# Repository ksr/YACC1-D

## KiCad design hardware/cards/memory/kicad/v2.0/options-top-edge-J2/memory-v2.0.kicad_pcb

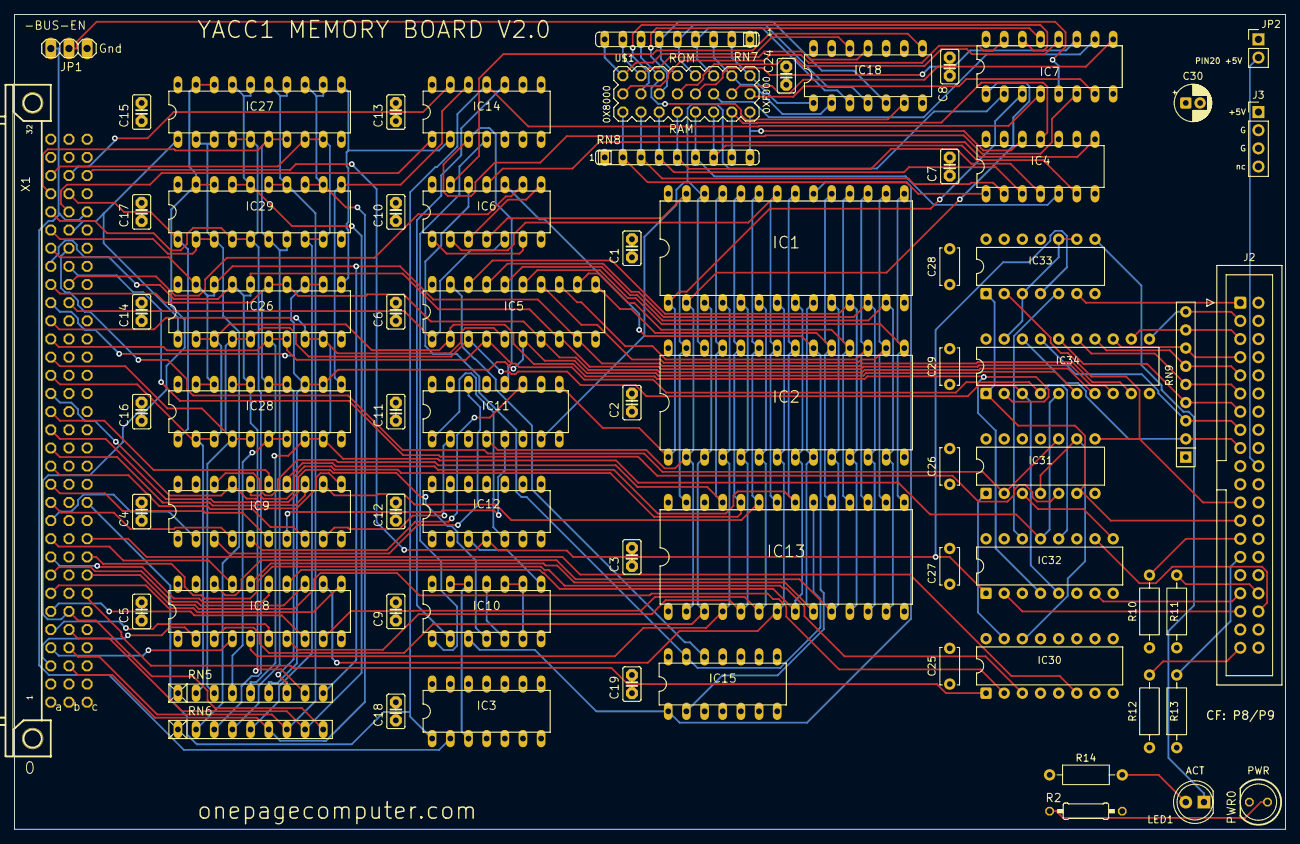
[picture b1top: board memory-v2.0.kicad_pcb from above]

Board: 4 copper layers, 177.8 x 114.0 mm, 70 parts (0 on the bottom side), 148 nets.

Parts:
C1, C2, C3, C4, C5, C6, C7, C8, C9, C10, C11, C12, C13, C14, C15, C16, C17, C18, C19, C24: C025-025X050
C25, C26, C27, C28, C29: 100n; C_Disc_D5.0mm_W2.5mm_P5.00mm
C30: 10u; CP_Radial_D5.0mm_P2.00mm
IC1, IC2, IC13: DIL28-6
IC3: 74LS32N; DIL14
IC4, IC18: 74ALS30N; DIL14
IC5: 74LS245N; DIL20
IC6, IC14: 74LS04N; DIL14
IC7: 74LS138N; DIL16
IC8, IC9: 74LS244N; DIL20
IC10: 74ALS00N; DIL14
IC11: 74LS157N; DIL16
IC12: 74LS74N; DIL14
IC15: 74ALS11N; DIL14
IC26, IC27, IC28, IC29: 74LS374N; DIL20
IC30: 74LS138; DIP-16_W7.62mm
IC31: 74LS32; DIP-14_W7.62mm
IC32: 74LS175; DIP-16_W7.62mm
IC33: 74LS08; DIP-14_W7.62mm
IC34: 74LS245; DIP-20_W7.62mm
J2: IDE 40; IDC-Header_2x20_P2.54mm_Vertical
J3: POWER; PinHeader_1x04_P2.54mm_Vertical
JP1: 1X03
JP2: PIN20 5V; PinHeader_1x02_P2.54mm_Vertical
LED1: ACT yellow; LED_D5.0mm
PWR0: LED5MM
R2: 330; 0207_10
R10, R11, R12, R13: 10k; R_Axial_DIN0207_L6.3mm_D2.5mm_P10.16mm_Horizontal
R14: 1k; R_Axial_DIN0207_L6.3mm_D2.5mm_P10.16mm_Horizontal
RN5, RN6: RN-9
RN7, RN8: SIL9
RN9: 10k x8; R_Array_SIP9
U$1: PIN_3X8
X1: FABC96R

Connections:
-BUS-EN: IC3.2, JP1.1, X1.C28
-HI-RAM: IC2.20, IC6.10, IC15.2
-IO-RD: IC31.5, X1.B25
-IO-WR: IC31.2, IC31.10, X1.B26
-LO-RAM: IC1.20, IC10.3, IC15.1
-MEM-RD: IC5.1, IC6.5, X1.B23
-MEM-WR: IC6.9, X1.B24
-RESET: IC12.4, IC32.1, IC33.4, X1.C30
-ROM-CS: IC6.12, IC13.20, IC15.13
-TMP-REG-LD0: IC14.1, X1.B28
-TMP-REG-LD1: IC14.13, X1.B30
-TMP-REG-RD0: IC26.1, IC27.1, X1.B27
-TMP-REG-RD1: IC28.1, IC29.1, X1.B29
-VMA: IC3.1, IC7.4, IC14.11, X1.C12
/Sheet 2/RAM0: IC4.1, RN8.2, U$1.17
/Sheet 2/RAM1: IC4.2, RN8.3, U$1.18
/Sheet 2/RAM2: IC4.3, RN8.4, U$1.19
/Sheet 2/RAM3: IC4.4, RN8.5, U$1.20
/Sheet 2/RAM4: IC4.5, RN8.6, U$1.21
/Sheet 2/RAM5: IC4.6, RN8.7, U$1.22
/Sheet 2/RAM6: IC4.11, RN8.8, U$1.23
/Sheet 2/RAM7: IC4.12, RN8.9, U$1.24
/Sheet 2/ROM0: IC18.12, RN7.9, U$1.1
/Sheet 2/ROM1: IC18.11, RN7.8, U$1.2
/Sheet 2/ROM2: IC18.6, RN7.7, U$1.3
/Sheet 2/ROM3: IC18.5, RN7.6, U$1.4
/Sheet 2/ROM4: IC18.4, RN7.5, U$1.5
/Sheet 2/ROM5: IC18.3, RN7.4, U$1.6
/Sheet 2/ROM6: IC18.2, RN7.3, U$1.7
/Sheet 2/ROM7: IC18.1, RN7.2, U$1.8
/Sheet 2/SEL0: IC7.15, U$1.9
/Sheet 2/SEL1: IC7.14, U$1.10
/Sheet 2/SEL2: IC7.13, U$1.11
/Sheet 2/SEL3: IC7.12, U$1.12
/Sheet 2/SEL4: IC7.11, U$1.13
/Sheet 2/SEL5: IC7.10, U$1.14
/Sheet 2/SEL6: IC7.9, U$1.15
/Sheet 2/SEL7: IC7.7, U$1.16
/Sheet 7/-CFOE: IC33.3, IC33.9, IC33.10, IC34.19
/Sheet 7/-CFRESET: IC33.6, J2.1
/Sheet 7/-DASP: J2.39, R12.2
/Sheet 7/-DMACK: J2.29, R13.2
/Sheet 7/-IOR: IC31.6, IC33.1, IC34.1, J2.25
/Sheet 7/-IOW: IC31.8, IC33.2, J2.23
/Sheet 7/-P8SEL: IC30.15, IC31.1
/Sheet 7/-P9SEL: IC30.14, IC31.4, IC31.9
/Sheet 7/-PDIAG: J2.34, R11.2
/Sheet 7/-SRST: IC32.14, IC33.5
/Sheet 7/ACTK: IC33.8, LED1.1
/Sheet 7/CFD0: IC34.18, J2.17, RN9.2
/Sheet 7/CFD1: IC34.17, J2.15, RN9.3
/Sheet 7/CFD2: IC34.16, J2.13, RN9.4
/Sheet 7/CFD3: IC34.15, J2.11, RN9.5
/Sheet 7/CFD4: IC34.14, J2.9, RN9.6
/Sheet 7/CFD5: IC34.13, J2.7, RN9.7
/Sheet 7/CFD6: IC34.12, J2.5, RN9.8
/Sheet 7/CFD7: IC34.11, J2.3, RN9.9
/Sheet 7/DA0: IC32.2, J2.35
/Sheet 7/DA1: IC32.7, J2.33
/Sheet 7/DA2: IC32.10, J2.36
/Sheet 7/IORDY: J2.27, R10.2
/Sheet 7/LATCHCLK: IC31.3, IC32.9
/Sheet 7/LEDA2: LED1.2, R14.2
/Sheet 7/PIN20: J2.20, JP2.2
ADDR0: IC8.2, X1.A3
ADDR1: IC8.4, X1.A4
ADDR2: IC8.6, X1.A5
ADDR3: IC8.8, X1.A6
ADDR4: IC8.11, X1.A7
ADDR5: IC8.13, X1.A8
ADDR6: IC8.15, X1.A9
ADDR7: IC8.17, X1.A10
ADDR8: IC9.2, X1.A11
ADDR9: IC9.4, X1.A12
ADDR10: IC9.6, X1.A13
ADDR11: IC9.8, X1.A14
ADDR12: IC9.11, X1.A15
ADDR13: IC9.13, X1.A16
ADDR14: IC9.15, X1.A17
ADDR15: IC9.17, IC10.4, X1.A18
BADDR0: IC1.10, IC2.10, IC8.18, IC13.10
BADDR1: IC1.9, IC2.9, IC8.16, IC13.9
BADDR2: IC1.8, IC2.8, IC8.14, IC13.8
BADDR3: IC1.7, IC2.7, IC8.12, IC13.7
BADDR4: IC1.6, IC2.6, IC8.9, IC13.6
BADDR5: IC1.5, IC2.5, IC8.7, IC13.5
BADDR6: IC1.4, IC2.4, IC8.5, IC13.4
BADDR7: IC1.3, IC2.3, IC8.3, IC13.3
BADDR8: IC1.25, IC2.25, IC9.18, IC13.25
BADDR9: IC1.24, IC2.24, IC9.16, IC13.24
BADDR10: IC1.21, IC2.21, IC9.14, IC13.21
BADDR11: IC1.23, IC2.23, IC9.12, IC13.23
BADDR12: IC1.2, IC2.2, IC7.1, IC11.4, IC13.2
BADDR13: IC1.26, IC2.26, IC7.2, IC11.7
BADDR14: IC1.1, IC2.1, IC7.3, IC11.9
BADDR15: IC7.6, IC11.12, IC14.3
BDATA0: IC1.11, IC2.11, IC5.18, IC13.11
BDATA1: IC1.12, IC2.12, IC5.17, IC13.12
BDATA2: IC1.13, IC2.13, IC5.16, IC13.13
BDATA3: IC1.15, IC2.15, IC5.15, IC13.15
BDATA4: IC1.16, IC2.16, IC5.14, IC13.16
BDATA5: IC1.17, IC2.17, IC5.13, IC13.17
BDATA6: IC1.18, IC2.18, IC5.12, IC13.18
BDATA7: IC1.19, IC2.19, IC5.11, IC13.19
DATA0: IC5.2, IC26.2, IC26.3, IC28.2, IC28.3, IC32.4, IC34.2, RN5.2, X1.A19
DATA1: IC5.3, IC26.4, IC26.5, IC28.4, IC28.5, IC32.5, IC34.3, RN5.3, X1.A20
DATA2: IC5.4, IC26.6, IC26.7, IC28.6, IC28.7, IC32.12, IC34.4, RN5.4, X1.A21
DATA3: IC5.5, IC26.8, IC26.9, IC28.8, IC28.9, IC32.13, IC34.5, RN5.5, X1.A22
DATA4: IC5.6, IC26.12, IC26.13, IC28.12, IC28.13, IC34.6, RN5.6, X1.A23
DATA5: IC5.7, IC26.14, IC26.15, IC28.14, IC28.15, IC34.7, RN5.7, X1.A24
DATA6: IC5.8, IC26.16, IC26.17, IC28.16, IC28.17, IC34.8, RN5.8, X1.A25
DATA7: IC5.9, IC26.18, IC26.19, IC28.18, IC28.19, IC34.9, RN5.9, X1.A26
DATA8: IC27.2, IC27.3, IC29.2, IC29.3, RN6.2, X1.A27
DATA9: IC27.4, IC27.5, IC29.4, IC29.5, RN6.3, X1.A28
DATA10: IC27.6, IC27.7, IC29.6, IC29.7, RN6.4, X1.A29
DATA11: IC27.8, IC27.9, IC29.8, IC29.9, RN6.5, X1.A30
DATA12: IC27.12, IC27.13, IC29.12, IC29.13, RN6.6, X1.B3
DATA13: IC27.14, IC27.15, IC29.14, IC29.15, RN6.7, X1.B4
DATA14: IC27.16, IC27.17, IC29.16, IC29.17, RN6.8, X1.B5
DATA15: IC27.18, IC27.19, IC29.18, IC29.19, RN6.9, X1.B6
FORCE-ROM: IC11.1, IC12.5
GND: C1.2, C2.2, C3.2, C4.2, C5.2, C6.2, C7.2, C8.2, C9.2, C10.2, C11.2, C12.2, C13.2, C14.2, C15.2, C16.2, C17.2, C18.2, C19.1, C24.1, C25.2, C26.2, C27.2, C28.2, C29.2, C30.2, IC1.14, IC2.14, IC3.4, IC3.5, IC3.7, IC3.9, IC3.10, IC3.12, IC3.13, IC4.7, IC5.10, IC6.7, IC7.8, IC8.1, IC8.10, IC8.19, IC9.1, IC9.10, IC9.19, IC10.7, IC11.8, IC11.15, IC12.2, IC12.7, IC12.10, IC12.11, IC12.12, IC12.13, IC13.14, IC14.7, IC15.3, IC15.4, IC15.5, IC15.7, IC15.9, IC15.10, IC15.11, IC18.7, IC26.10, IC27.10, IC28.10, IC29.10, IC30.4, IC30.5, IC30.8, IC31.7, IC31.12, IC31.13, IC32.8, IC33.7, IC33.12, IC33.13, IC34.10, J2.2, J2.19, J2.22, J2.24, J2.26, J2.28, J2.30, J2.37, J2.40, J3.2, J3.3, JP1.3, PWR0.K, RN5.1, RN6.1, X1.A1, X1.A32, X1.B1, X1.B32, X1.C1, X1.C32
IO-ADDR0: IC30.1, X1.C7
IO-ADDR1: IC30.2, X1.C8
IO-ADDR2: IC30.3, X1.C9
IO-ADDR3: IC30.6, X1.C10
unnamed: IC1.22, IC2.22, IC6.2, IC13.22
unnamed: IC1.27, IC2.27, IC6.4, IC13.27
unnamed: IC4.8, IC6.11
unnamed: IC6.1, IC6.6
unnamed: IC6.3, IC6.8
unnamed: IC7.5, JP1.2
unnamed: IC10.1, IC14.4
unnamed: IC10.2, IC14.10
unnamed: IC10.5, IC10.11
unnamed: IC10.6, IC10.9, IC10.10
unnamed: IC10.8, IC12.3
unnamed: IC3.3, IC10.12, IC10.13
unnamed: IC9.9, IC11.2
unnamed: IC9.7, IC11.5
unnamed: IC9.5, IC11.11
unnamed: IC9.3, IC11.14
unnamed: IC14.2, IC26.11, IC27.11
unnamed: IC14.12, IC28.11, IC29.11
unnamed: IC5.19, IC15.12
unnamed: IC6.13, IC18.8
unnamed: PWR0.A, R2.1
VCC: C1.1, C2.1, C3.1, C4.1, C5.1, C6.1, C7.1, C8.1, C9.1, C10.1, C11.1, C12.1, C13.1, C14.1, C15.1, C16.1, C17.1, C18.1, C19.2, C24.2, C25.1, C26.1, C27.1, C28.1, C29.1, C30.1, IC1.28, IC2.28, IC3.14, IC4.14, IC5.20, IC6.14, IC7.16, IC8.20, IC9.20, IC10.14, IC11.3, IC11.6, IC11.10, IC11.13, IC11.16, IC12.1, IC12.14, IC13.28, IC14.14, IC15.14, IC18.14, IC26.20, IC27.20, IC28.20, IC29.20, IC30.16, IC31.14, IC32.16, IC33.14, IC34.20, J2.38, J3.1, JP2.1, R2.2, R10.1, R11.1, R12.1, R13.1, R14.1, RN7.1, RN8.1, RN9.1, X1.A2, X1.A31, X1.B2, X1.B31, X1.C2, X1.C31

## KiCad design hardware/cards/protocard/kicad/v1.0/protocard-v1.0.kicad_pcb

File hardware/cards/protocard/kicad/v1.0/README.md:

# protocard-v1.0 — KiCad conversion

Generated 2026-09-23 by `tools/eagle_to_kicad_all.py` from the Eagle design `ProtoCard-Prod-V1.0` in `hardware/cards/protocard/eagle/v1.0/`. **The Eagle files are the record of what was designed and built; this KiCad project is derived from them and is regenerated from scratch on every run of the tool** (hand edits here will be lost - once a card is edited in KiCad, remove it from the tool's list). This revision was FABRICATED (see `hardware/FABRICATED.md`).

## Files

| File | What it is |
|---|---|
| `protocard-v1.0.kicad_pro` | project; OSH Park rules (6 mil track, 5 mil clearance, 10 mil drill, 4 mil annular) |
| `protocard-v1.0.kicad_sch` | root sheet; 1 sub-sheet(s) `protocard-v1.0-sheetN.kicad_sch` mirror the Eagle sheets |
| `protocard-v1.0-eagle.kicad_sym` | project symbol library generated from the Eagle libraries used (units = Eagle gates) |
| `protocard-v1.0.kicad_pcb` | the board: 2 copper layers, 9 footprints, 319 track segments, 0 vias |
| `protocard-v1.0-eagle.pretty/` | project footprint library extracted from the imported board |
| `reports/` | ERC (`erc.json`), DRC (`drc.json`), schematic PDF, board renders (`-top.png`, `-bottom.png`), netlist + `netlist-compare.txt` |

## Proof

Schematic-vs-board netlist comparison (`tools/kicad/compare_netlists.py`: every (reference, pad) partition must be identical): **MATCH (87/87 nets)**

```
  same connectivity, different net name: [('/Sheet 1/AC-IN-INV', 'AC-IN-INV'), ('/Sheet 1/ADDR-REG-CLK', 'ADDR-REG-CLK'), ('/Sheet 1/ADDR-REG-OUT', 'ADDR-REG-OUT'), ('/Sheet 1/ADDR0', 'ADDR0'), ('/Sheet 1/ADDR1', 'ADDR1'), ('/Sheet 1/ADDR2', 'ADDR2'), ('/Sheet 1/ADDR3', 'ADDR3'), ('/Sheet 1/ADDR4', 'ADDR4'), ('/Sheet 1/ADDR5', 'ADDR5'), ('/Sheet 1/ADDR6', 'ADDR6'), ('/Sheet 1/ADDR7', 'ADDR7'), ('/Sheet 1/ADDR8', 'ADDR8'), ('/Sheet 1/ADDR9', 'ADDR9'), ('/Sheet 1/ADDR10', 'ADDR10'), ('/Sheet 1/ADDR11', 'ADDR11'), ('/Sheet 1/ADDR12', 'ADDR12'), ('/Sheet 1/ADDR13', 'ADDR13'), ('/Sheet 1/ADDR14', 'ADDR14'), ('/Sheet 1/ADDR15', 'ADDR15'), ('/Sheet 1/ALU-FUNC', 'ALU-FUNC'), ('/Sheet 1/ALU0', 'ALU0'), ('/Sheet 1/ALU1', 'ALU1'), ('/Sheet 1/ALU2', 'ALU2'), ('/Sheet 1/ALU3', 'ALU3'), ('/Sheet 1/BR-COND', 'BR-COND'), ('/Sheet 1/BR-REG-LD-HI', 'BR-REG-LD-HI'), ('/Sheet 1/BR-REG-LD-LO', 'BR-REG-LD-LO'), ('/Sheet 1/BR-REG-OUT', 'BR-REG-OUT'), ('/Sheet 1/BRD-ADDR-REG0', 'BRD-ADDR-REG0'), ('/Sheet 1/BRD-ADDR-REG1', 'BRD-ADDR-REG1'), ('/Sheet 1/BRD-IN-ID0', 'BRD-IN-ID0'), ('/Sheet 1/BRD-IN-ID1', 'BRD-IN-ID1'), ('/Sheet 1/BRD-OUT-ID0', 'BRD-OUT-ID0'), ('/Sheet 1/BRD-OUT-ID1', 'BRD-OUT-ID1'), ('/Sheet 1/DATA-REG-IN-ID0', 'DATA-REG-IN-ID0'), ('/Sheet 1/DATA-REG-IN-ID1', 'DATA-REG-IN-ID1'), ('/Sheet 1/DATA-REG-OUT-ID0', 'DATA-REG-OUT-ID0'), ('/Sheet 1/DATA-REG-OUT-ID1', 'DATA-REG-OUT-ID1'), ('/Sheet 1/DATA-REG-RD-HI', 'DATA-REG-RD-HI'), ('/Sheet 1/DATA-REG-RD-LO', 'DATA-REG-RD-LO'), ('/Sheet 1/DATA-REG-WR-HI', 'DATA-REG-WR-HI'), ('/Sheet 1/DATA-REG-WR-LO', 'DATA-REG-WR-LO'), ('/Sheet 1/DATA0', 'DATA0'), ('/Sheet 1/DATA1', 'DATA1'), ('/Sheet 1/DATA2', 'DATA2'), ('/Sheet 1/DATA3', 'DATA3'), ('/Sheet 1/DATA4', 'DATA4'), ('/Sheet 1/DATA5', 'DATA5'), ('/Sheet 1/DATA6', 'DATA6'), ('/Sheet 1/DATA7', 'DATA7'), ('/Sheet 1/DATA8', 'DATA8'), ('/Sheet 1/DATA9', 'DATA9'), ('/Sheet 1/DATA10', 'DATA10'), ('/Sheet 1/DATA11', 'DATA11'), ('/Sheet 1/DATA12', 'DATA12'), ('/Sheet 1/DATA13', 'DATA13'), ('/Sheet 1/DATA14', 'DATA14'), ('/Sheet 1/DATA15', 'DATA15'), ('/Sheet 1/DIR', 'DIR'), ('/Sheet 1/H{slash}L-SWAP', 'H/L-SWAP'), ('/Sheet 1/INT', 'INT'), ('/Sheet 1/INT-ACK', 'INT-ACK'), ('/Sheet 1/IO-ADDR', 'IO-ADDR'), ('/Sheet 1/I{slash}D-REG-DN', 'I/D-REG-DN'), ('/Sheet 1/I{slash}D-REG-LD', 'I/D-REG-LD'), ('/Sheet 1/I{slash}D-REG-OUT', 'I/D-REG-OUT'), ('/Sheet 1/I{slash}D-REG-UP', 'I/D-REG-UP'), ('/Sheet 1/I{slash}O-RD', 'I/O-RD'), ('/Sheet 1/I{slash}O-WR', 'I/O-WR'), ('/Sheet 1/LD-AC', 'LD-AC'), ('/Sheet 1/MEM-RD', 'MEM-RD'), ('/Sheet 1/MEM-WR', 'MEM-WR'), ('/Sheet 1/RD-AC', 'RD-AC'), ('/Sheet 1/REG-FUNC', 'REG-FUNC'), ('/Sheet 1/RESET', 'RESET'), ('/Sheet 1/SP{slash}PC-ADDR-OUT', 'SP/PC-ADDR-OUT'), ('/Sheet 1/SP{slash}PC-DATA-OUT-HI', 'SP/PC-DATA-OUT-HI'), ('/Sheet 1/SP{slash}PC-DATA-OUT-LO', 'SP/PC-DATA-OUT-LO'), ('/Sheet 1/SP{slash}PC-DN', 'SP/PC-DN'), ('/Sheet 1/SP{slash}PC-LD-HI', 'SP/PC-LD-HI'), ('/Sheet 1/SP{slash}PC-LD-LO', 'SP/PC-LD-LO'), ('/Sheet 1/SP{slash}PC-SEL', 'SP/PC-SEL'), ('/Sheet 1/SP{slash}PC-UP', 'SP/PC-UP'), ('/Sheet 1/SR-LD', 'SR-LD'), ('Net-(PWR0-PadA)', 'N$10')]
```

## Readability

`tools/kicad/sch_overlaps.py` over every sheet: text over text 7, text over a symbol body 14, text crossed by a line 0, items off the drawing frame or on the title block 0. What is left is mostly the Eagle drawing itself (parts placed that close in Eagle) or KiCad drawing pin numbers centred on short pins.

## Residual ERC / DRC

ERC by type: none.
`isolated_pin_label` = the converter's per-net global labels (cosmetic); `power_pin_not_driven` / unused-unit notes are the same ones KiCad's own Eagle importer leaves. `unconnected_wire_endpoint` / `pin_not_connected` = wire stubs Eagle leaves bare (mostly net wires ending on a bus, which is drawn as graphics here); since 2026-09-23 the converter no longer hangs a label on every such end (that was most of the label clutter), so they show as KiCad warnings.

DRC by type: items_not_allowed 2, lib_footprint_mismatch 1, silk_edge_clearance 5, silk_over_copper 199, silk_overlap 59, text_height 2; unconnected items 0; schematic parity 0.
Silk-over-pad and clearance notes reflect the Eagle design as drawn; unconnected items are Eagle airwires (parts the design left unrouted).

Converter: converted: 106 symbols, 141 wires, 84 labels, 23 junctions, 0 bus lines, 0 no-connects

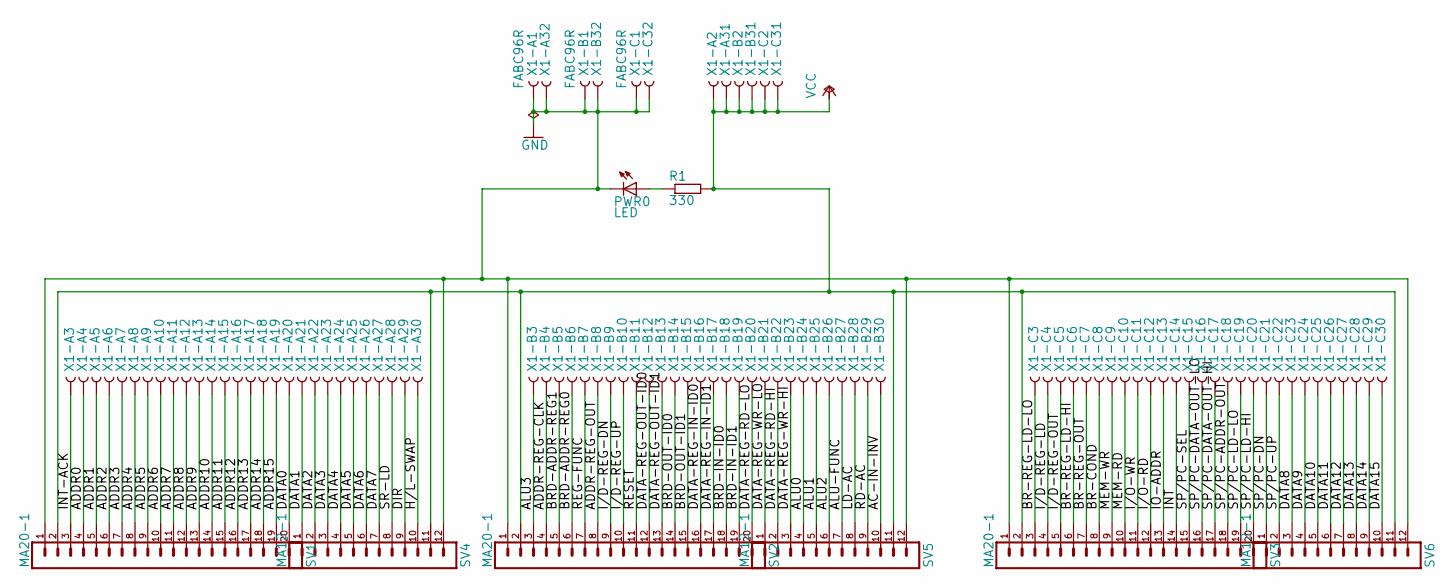
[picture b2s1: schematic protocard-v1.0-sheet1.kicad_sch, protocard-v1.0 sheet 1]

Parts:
PWR0: LED; LED5MM
R1: 330; 0207_10
SV1, SV2, SV3: MA20-1
SV4, SV5, SV6: MA12-1
X1: FABC96R

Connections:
AC-IN-INV: SV5.10, X1.B30
ADDR0: SV1.4, X1.A4
ADDR1: SV1.5, X1.A5
ADDR2: SV1.6, X1.A6
ADDR3: SV1.7, X1.A7
ADDR4: SV1.8, X1.A8
ADDR5: SV1.9, X1.A9
ADDR6: SV1.10, X1.A10
ADDR7: SV1.11, X1.A11
ADDR8: SV1.12, X1.A12
ADDR9: SV1.13, X1.A13
ADDR10: SV1.14, X1.A14
ADDR11: SV1.15, X1.A15
ADDR12: SV1.16, X1.A16
ADDR13: SV1.17, X1.A17
ADDR14: SV1.18, X1.A18
ADDR15: SV1.19, X1.A19
ADDR-REG-CLK: SV2.4, X1.B4
ADDR-REG-OUT: SV2.8, X1.B8
ALU0: SV5.4, X1.B24
ALU1: SV5.5, X1.B25
ALU2: SV5.6, X1.B26
ALU3: SV2.3, X1.B3
ALU-FUNC: SV5.7, X1.B27
BR-COND: SV3.8, X1.C8
BR-REG-LD-HI: SV3.6, X1.C6
BR-REG-LD-LO: SV3.3, X1.C3
BR-REG-OUT: SV3.7, X1.C7
BRD-ADDR-REG0: SV2.6, X1.B6
BRD-ADDR-REG1: SV2.5, X1.B5
BRD-IN-ID0: SV2.18, X1.B18
BRD-IN-ID1: SV2.19, X1.B19
BRD-OUT-ID0: SV2.14, X1.B14
BRD-OUT-ID1: SV2.15, X1.B15
DATA0: SV1.20, X1.A20
DATA1: SV4.1, X1.A21
DATA2: SV4.2, X1.A22
DATA3: SV4.3, X1.A23
DATA4: SV4.4, X1.A24
DATA5: SV4.5, X1.A25
DATA6: SV4.6, X1.A26
DATA7: SV4.7, X1.A27
DATA8: SV6.3, X1.C23
DATA9: SV6.4, X1.C24
DATA10: SV6.5, X1.C25
DATA11: SV6.6, X1.C26
DATA12: SV6.7, X1.C27
DATA13: SV6.8, X1.C28
DATA14: SV6.9, X1.C29
DATA15: SV6.10, X1.C30
DATA-REG-IN-ID0: SV2.16, X1.B16
DATA-REG-IN-ID1: SV2.17, X1.B17
DATA-REG-OUT-ID0: SV2.12, X1.B12
DATA-REG-OUT-ID1: SV2.13, X1.B13
DATA-REG-RD-HI: SV5.2, X1.B22
DATA-REG-RD-LO: SV2.20, X1.B20
DATA-REG-WR-HI: SV5.3, X1.B23
DATA-REG-WR-LO: SV5.1, X1.B21
DIR: SV4.9, X1.A29
GND: PWR0.K (C), SV1.1, SV2.1, SV3.1, SV4.12, SV5.12, SV6.12, X1.A1, X1.A32, X1.B1, X1.B32, X1.C1, X1.C32
H/L-SWAP: SV4.10, X1.A30
I/D-REG-DN: SV2.9, X1.B9
I/D-REG-LD: SV3.4, X1.C4
I/D-REG-OUT: SV3.5, X1.C5
I/D-REG-UP: SV2.10, X1.B10
I/O-RD: SV3.12, X1.C12
I/O-WR: SV3.11, X1.C11
INT: SV3.14, X1.C14
INT-ACK: SV1.3, X1.A3
IO-ADDR: SV3.13, X1.C13
LD-AC: SV5.8, X1.B28
MEM-RD: SV3.10, X1.C10
MEM-WR: SV3.9, X1.C9
unnamed: PWR0.A, R1.1
RD-AC: SV5.9, X1.B29
REG-FUNC: SV2.7, X1.B7
RESET: SV2.11, X1.B11
SP/PC-ADDR-OUT: SV3.18, X1.C18
SP/PC-DATA-OUT-HI: SV3.17, X1.C17
SP/PC-DATA-OUT-LO: SV3.16, X1.C16
SP/PC-DN: SV6.1, X1.C21
SP/PC-LD-HI: SV3.20, X1.C20
SP/PC-LD-LO: SV3.19, X1.C19
SP/PC-SEL: SV3.15, X1.C15
SP/PC-UP: SV6.2, X1.C22
SR-LD: SV4.8, X1.A28
VCC: R1.2, SV1.2, SV2.2, SV3.2, SV4.11, SV5.11, SV6.11, X1.A2, X1.A31, X1.B2, X1.B31, X1.C2, X1.C31

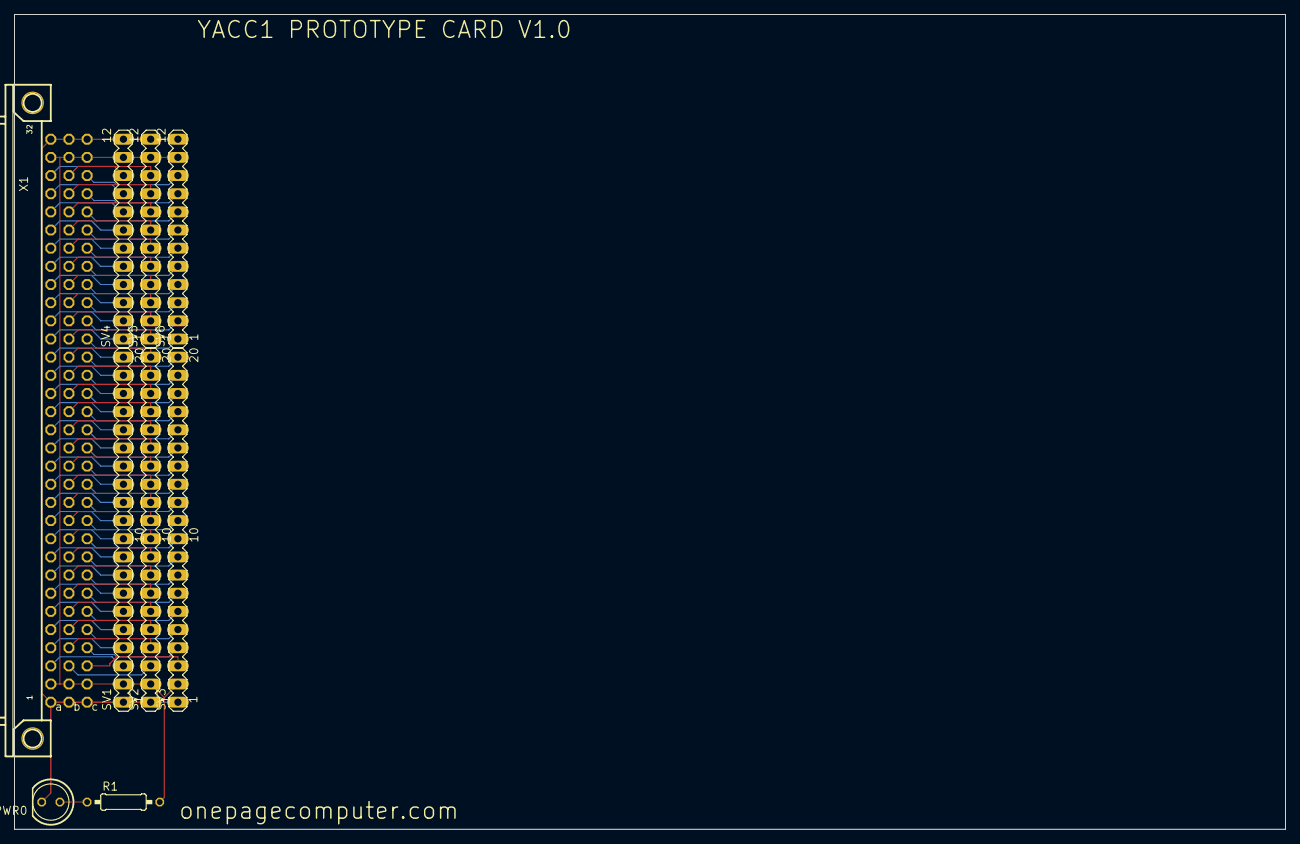
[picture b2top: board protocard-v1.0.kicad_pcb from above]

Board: 2 copper layers, 177.8 x 114.0 mm, 9 parts (0 on the bottom side), 87 nets.

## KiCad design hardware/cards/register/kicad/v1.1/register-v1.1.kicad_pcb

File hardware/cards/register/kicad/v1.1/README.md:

# register-v1.1 — KiCad conversion

Generated 2026-09-23 by `tools/eagle_to_kicad_all.py` from the Eagle design `Index Registers - 1.1` in `hardware/cards/register/eagle/v1.1/`. **The Eagle files are the record of what was designed and built; this KiCad project is derived from them and is regenerated from scratch on every run of the tool** (hand edits here will be lost - once a card is edited in KiCad, remove it from the tool's list). This revision was FABRICATED (see `hardware/FABRICATED.md`).

## Files

| File | What it is |
|---|---|
| `register-v1.1.kicad_pro` | project; OSH Park rules (6 mil track, 5 mil clearance, 10 mil drill, 4 mil annular) |
| `register-v1.1.kicad_sch` | root sheet; 8 sub-sheet(s) `register-v1.1-sheetN.kicad_sch` mirror the Eagle sheets |
| `register-v1.1-eagle.kicad_sym` | project symbol library generated from the Eagle libraries used (units = Eagle gates) |
| `register-v1.1.kicad_pcb` | the board: 4 copper layers, 102 footprints, 3591 track segments, 544 vias |
| `register-v1.1-eagle.pretty/` | project footprint library extracted from the imported board |
| `reports/` | ERC (`erc.json`), DRC (`drc.json`), schematic PDF, board renders (`-top.png`, `-bottom.png`), netlist + `netlist-compare.txt` |

## Proof

Schematic-vs-board netlist comparison (`tools/kicad/compare_netlists.py`: every (reference, pad) partition must be identical): **MATCH (223/223 nets)**

```
  same connectivity, different net name: [('/Sheet 6/-ADDRSEL', '-ADDRSEL'), ('/Sheet 6/-ARD0', '-ARD0'), ('/Sheet 6/-RLD0', '-RLD0'), ('/Sheet 6/-RRD0', '-RRD0'), ('/Sheet 7/BUS-DIR', 'BUS-DIR'), ('Net-(IC1A-O)', 'N$17'), ('Net-(IC1B-O)', 'N$18'), ('Net-(IC1C-O)', 'N$16'), ('Net-(IC1D-O)', 'N$22'), ('Net-(IC2A-O)', 'N$20'), ('Net-(IC2B-O)', 'N$21'), ('Net-(IC3-BO)', 'N$10'), ('Net-(IC3-CO)', 'N$11'), ('Net-(IC3-QA)', 'N$115'), ('Net-(IC3-QB)', 'N$116'), ('Net-(IC3-QC)', 'N$117'), ('Net-(IC3-QD)', 'N$118'), ('Net-(IC4-BO)', 'N$12'), ('Net-(IC4-CO)', 'N$13'), ('Net-(IC4-QA)', 'N$119'), ('Net-(IC4-QB)', 'N$120'), ('Net-(IC4-QC)', 'N$121'), ('Net-(IC4-QD)', 'N$122'), ('Net-(IC5-BO)', 'N$14'), ('Net-(IC5-CO)', 'N$15'), ('Net-(IC10-BO)', 'N$4'), ('Net-(IC10-CO)', 'N$5'), ('Net-(IC10-DN)', 'N$2'), ('Net-(IC10-LD)', 'N$8'), ('Net-(IC10-QA)', 'N$32'), ('Net-(IC10-QB)', 'N$33'), ('Net-(IC10-QC)', 'N$34'), ('Net-(IC10-QD)', 'N$35'), ('Net-(IC10-UP)', 'N$3'), ('Net-(IC11-BO)', 'N$6'), ('Net-(IC11-CO)', 'N$7'), ('Net-(IC11-LD)', 'N$27'), ('Net-(IC11-QA)', 'N$36'), ('Net-(IC11-QB)', 'N$38'), ('Net-(IC11-QC)', 'N$39'), ('Net-(IC11-QD)', 'N$40'), ('Net-(IC12-QA)', 'N$54'), ('Net-(IC12-QB)', 'N$55'), ('Net-(IC12-QC)', 'N$56'), ('Net-(IC12-QD)', 'N$57'), ('Net-(IC13A-G)', 'N$25'), ('Net-(IC13B-A1)', 'N$28'), ('Net-(IC13B-A2)', 'N$29'), ('Net-(IC13B-A3)', 'N$30'), ('Net-(IC13B-A4)', 'N$31'), ('Net-(IC14A-G)', 'N$26'), ('Net-(IC15A-O)', 'N$9'), ('Net-(IC15B-O)', 'N$23'), ('Net-(IC19-BO)', 'N$58'), ('Net-(IC19-CO)', 'N$59'), ('Net-(IC19-DN)', 'N$66'), ('Net-(IC19-LD)', 'N$64'), ('Net-(IC19-QA)', 'N$70'), ('Net-(IC19-QB)', 'N$71'), ('Net-(IC19-QC)', 'N$72'), ('Net-(IC19-QD)', 'N$73'), ('Net-(IC19-UP)', 'N$65'), ('Net-(IC20-BO)', 'N$60'), ('Net-(IC20-CO)', 'N$61'), ('Net-(IC20-QA)', 'N$74'), ('Net-(IC20-QB)', 'N$75'), ('Net-(IC20-QC)', 'N$76'), ('Net-(IC20-QD)', 'N$77'), ('Net-(IC21-BO)', 'N$62'), ('Net-(IC21-CO)', 'N$63'), ('Net-(IC21-LD)', 'N$69'), ('Net-(IC21-QA)', 'N$78'), ('Net-(IC21-QB)', 'N$79'), ('Net-(IC21-QC)', 'N$80'), ('Net-(IC21-QD)', 'N$81'), ('Net-(IC22-QA)', 'N$82'), ('Net-(IC22-QB)', 'N$83'), ('Net-(IC22-QC)', 'N$84'), ('Net-(IC22-QD)', 'N$85'), ('Net-(IC23A-G)', 'N$67'), ('Net-(IC24A-G)', 'N$68'), ('Net-(IC26C-O)', 'N$95'), ('Net-(IC26D-O)', 'N$96'), ('Net-(IC29-BO)', 'N$86'), ('Net-(IC29-CO)', 'N$87'), ('Net-(IC29-DN)', 'N$94'), ('Net-(IC29-LD)', 'N$92'), ('Net-(IC29-QA)', 'N$98'), ('Net-(IC29-QB)', 'N$99'), ('Net-(IC29-QC)', 'N$100'), ('Net-(IC29-QD)', 'N$101'), ('Net-(IC29-UP)', 'N$93'), ('Net-(IC30-BO)', 'N$88'), ('Net-(IC30-CO)', 'N$89'), ('Net-(IC30-QA)', 'N$102'), ('Net-(IC30-QB)', 'N$103'), ('Net-(IC30-QC)', 'N$104'), ('Net-(IC30-QD)', 'N$105'), ('Net-(IC31A-O)', 'N$19'), ('Net-(IC31B-O)', 'N$24'), ('Net-(IC31C-I0)', 'N$41'), ('Net-(IC31C-I1)', 'N$42'), ('Net-(IC31C-O)', 'N$1'), ('Net-(IC31D-O)', 'N$37'), ('Net-(IC32A-Y1)', 'N$43'), ('Net-(IC32A-Y2)', 'N$46'), ('Net-(IC32A-Y3)', 'N$47'), ('Net-(IC32B-Y1)', 'N$48'), ('Net-(IC32B-Y2)', 'N$49'), ('Net-(IC32B-Y3)', 'N$50'), ('Net-(IC38B-G)', 'N$45'), ('Net-(IC38B-Y1)', 'N$51'), ('Net-(IC38B-Y2)', 'N$52'), ('Net-(IC38B-Y3)', 'N$53'), ('Net-(IC42A-A1)', 'N$123'), ('Net-(IC42A-A2)', 'N$124'), ('Net-(IC42A-A3)', 'N$125'), ('Net-(IC42A-A4)', 'N$126'), ('Net-(IC42B-A1)', 'N$127'), ('Net-(IC42B-A2)', 'N$128'), ('Net-(IC42B-A3)', 'N$129'), ('Net-(IC42B-A4)', 'N$130'), ('Net-(IC43-BO)', 'N$90'), ('Net-(IC43-CO)', 'N$91'), ('Net-(IC43-LD)', 'N$97'), ('Net-(IC43-QA)', 'N$106'), ('Net-(IC43-QB)', 'N$107'), ('Net-(IC43-QC)', 'N$108'), ('Net-(IC43-QD)', 'N$109'), ('Net-(IC44-QA)', 'N$110'), ('Net-(IC44-QB)', 'N$111'), ('Net-(IC44-QC)', 'N$112'), ('Net-(IC44-QD)', 'N$113'), ('Net-(PWR0-PadA)', 'N$44')]
```

## Readability

`tools/kicad/sch_overlaps.py` over every sheet: text over text 0, text over a symbol body 18, text crossed by a line 28, items off the drawing frame or on the title block 0. What is left is mostly the Eagle drawing itself (parts placed that close in Eagle) or KiCad drawing pin numbers centred on short pins.

## Residual ERC / DRC

ERC by type: endpoint_off_grid 89, isolated_pin_label 28, unconnected_wire_endpoint 52.
`isolated_pin_label` = the converter's per-net global labels (cosmetic); `power_pin_not_driven` / unused-unit notes are the same ones KiCad's own Eagle importer leaves. `unconnected_wire_endpoint` / `pin_not_connected` = wire stubs Eagle leaves bare (mostly net wires ending on a bus, which is drawn as graphics here); since 2026-09-23 the converter no longer hangs a label on every such end (that was most of the label clutter), so they show as KiCad warnings.

DRC by type: clearance 30, items_not_allowed 2, lib_footprint_mismatch 1, shorting_items 2, silk_edge_clearance 4, silk_over_copper 199, silk_overlap 1, text_height 2, track_width 199; unconnected items 0; schematic parity 0.
Silk-over-pad and clearance notes reflect the Eagle design as drawn; unconnected items are Eagle airwires (parts the design left unrouted).

Converter: converted: 276 symbols, 1273 wires, 445 labels, 239 junctions, 21 bus lines, 11 no-connects

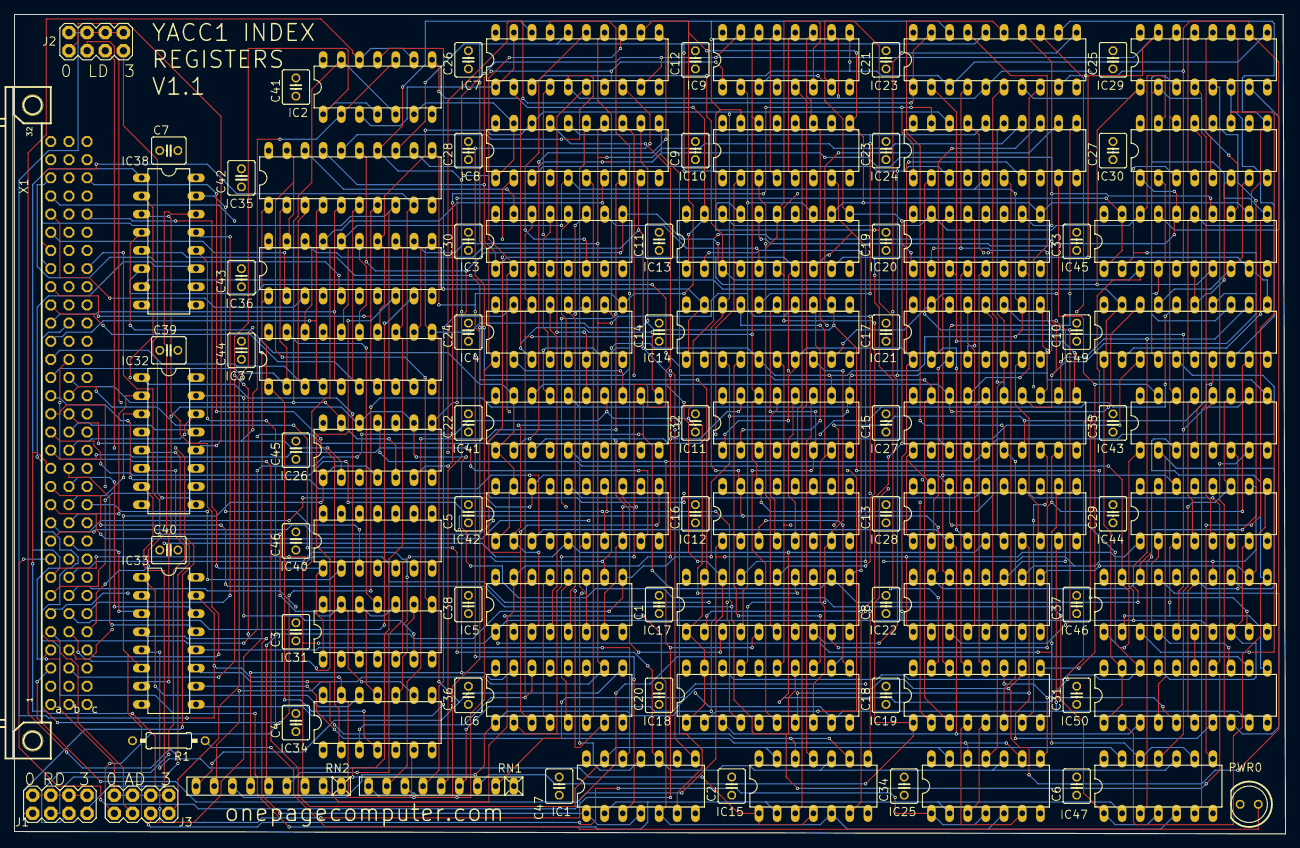
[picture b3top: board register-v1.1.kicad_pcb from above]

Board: 4 copper layers, 177.8 x 114.6 mm, 102 parts (0 on the bottom side), 223 nets.

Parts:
C1, C2, C3, C4, C5, C6, C7, C8, C9, C10, C11, C12, C13, C14, C15, C16, C17, C18, C19, C20, C21, C22, C23, C24, C25, C26, C27, C28, C29, C30, C31, C32, C33, C34, C35, C36, C37, C38, C39, C40, C41, C42, C43, C44, C45, C46, C47: 0.1; C025-040X050
IC1, IC2, IC15, IC25, IC26, IC31, IC40, IC47: 74LS32N; DIL14
IC3, IC4, IC5, IC6, IC9, IC10, IC11, IC12, IC19, IC20, IC21, IC22, IC29, IC30, IC43, IC44: 74LS192N; DIL16
IC7, IC8, IC13, IC14, IC17, IC18, IC23, IC24, IC27, IC28, IC41, IC42, IC45, IC46, IC49, IC50: 74LS244N; DIL20
IC32, IC33, IC38: 74LS139N; DIL16
IC34: 4077N; DIL14
IC35, IC36, IC37: 74LS245N; DIL20
J1, J2, J3: 2X4
PWR0: LED5MM
R1: 330; 0207_10
RN1, RN2: 10k; RN-9
X1: FABC96R

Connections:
-ADDRSEL: IC38.1, J3.2, J3.4, J3.6, J3.8
-ARD0: IC38.12, J3.1
-BUS-EN: IC31.1, IC31.4, IC40.1, X1.C28
-HL-SWAP: IC31.13, IC34.9, X1.C25
-LDSEL: IC33.15, IC34.6, IC34.13, J2.2, J2.4, J2.6, J2.8
-R0-ADDRSEL: IC38.4, IC41.1, IC41.19, IC42.1, IC42.19
-R0-LDSEL: IC1.9, IC1.12, IC33.12
-R0-RDSEL: IC1.1, IC1.4, IC2.1, IC2.4, IC33.4
-R1-ADDRSEL: IC17.1, IC17.19, IC18.1, IC18.19, IC38.5
-R1-LDSEL: IC15.9, IC15.12, IC33.11
-R1-RDSEL: IC2.9, IC2.12, IC15.1, IC15.4, IC33.5
-R2-ADDRSEL: IC27.1, IC27.19, IC28.1, IC28.19, IC38.6
-R2-LDSEL: IC25.9, IC25.12, IC33.10
-R2-RDSEL: IC25.1, IC25.4, IC26.1, IC26.4, IC33.6
-R3-ADDRSEL: IC38.7, IC49.1, IC49.19, IC50.1, IC50.19
-R3-LDSEL: IC33.9, IC47.9, IC47.12
-R3-RDSEL: IC26.9, IC26.12, IC33.7, IC47.1, IC47.4
-RDSEL: IC33.1, IC34.12, J1.2, J1.4, J1.6, J1.8
-REG-DN: IC1.5, IC15.5, IC25.5, IC47.5, X1.B21
-REG-FUNC-LD: IC31.5, X1.B8
-REG-FUNC-RD: IC31.2, X1.B7
-REG-LD-HI: IC1.13, IC15.13, IC25.13, IC47.13, X1.B20
-REG-LD-LO: IC1.10, IC15.10, IC25.10, IC47.10, X1.B18
-REG-RD-HI: IC2.5, IC2.13, IC26.5, IC26.13, X1.B19
-REG-RD-LO: IC2.2, IC2.10, IC26.2, IC26.10, X1.B17
-REG-UP: IC1.2, IC15.2, IC25.2, IC47.2, X1.B22
-RESET: IC34.2, X1.C30
-RLD0: IC32.12, J2.1
-RRD0: IC32.4, J1.1
-VMA: IC40.2, X1.C12
ADATA0: IC3.15, IC7.9, IC9.15, IC13.9, IC19.15, IC23.9, IC29.15, IC35.18, IC45.9, RN1.2
ADATA1: IC3.1, IC7.7, IC9.1, IC13.7, IC19.1, IC23.7, IC29.1, IC35.17, IC45.7, RN1.3
ADATA2: IC3.10, IC7.5, IC9.10, IC13.5, IC19.10, IC23.5, IC29.10, IC35.16, IC45.5, RN1.4
ADATA3: IC3.9, IC7.3, IC9.9, IC13.3, IC19.9, IC23.3, IC29.9, IC35.15, IC45.3, RN1.5
ADATA4: IC4.15, IC7.18, IC10.15, IC13.18, IC20.15, IC23.18, IC30.15, IC35.14, IC45.18, RN1.6
ADATA5: IC4.1, IC7.16, IC10.1, IC13.16, IC20.1, IC23.16, IC30.1, IC35.13, IC45.16, RN1.7
ADATA6: IC4.10, IC7.14, IC10.10, IC13.14, IC20.10, IC23.14, IC30.10, IC35.12, IC45.14, RN1.8
ADATA7: IC4.9, IC7.12, IC10.9, IC13.12, IC20.9, IC23.12, IC30.9, IC35.11, IC45.12, RN1.9
ADATA8: IC5.15, IC8.9, IC11.15, IC14.9, IC21.15, IC24.9, IC36.18, IC37.18, IC43.15, IC46.9, RN2.2
ADATA9: IC5.1, IC8.7, IC11.1, IC14.7, IC21.1, IC24.7, IC36.17, IC37.17, IC43.1, IC46.7, RN2.3
ADATA10: IC5.10, IC8.5, IC11.10, IC14.5, IC21.10, IC24.5, IC36.16, IC37.16, IC43.10, IC46.5, RN2.4
ADATA11: IC5.9, IC8.3, IC11.9, IC14.3, IC21.9, IC24.3, IC36.15, IC37.15, IC43.9, IC46.3, RN2.5
ADATA12: IC6.15, IC8.18, IC12.15, IC14.18, IC22.15, IC24.18, IC36.14, IC37.14, IC44.15, IC46.18, RN2.6
ADATA13: IC6.1, IC8.16, IC12.1, IC14.16, IC22.1, IC24.16, IC36.13, IC37.13, IC44.1, IC46.16, RN2.7
ADATA14: IC6.10, IC8.14, IC12.10, IC14.14, IC22.10, IC24.14, IC36.12, IC37.12, IC44.10, IC46.14, RN2.8
ADATA15: IC6.9, IC8.12, IC12.9, IC14.12, IC22.9, IC24.12, IC36.11, IC37.11, IC44.9, IC46.12, RN2.9
ADDR0: IC17.18, IC27.18, IC41.18, IC49.18, X1.A3
ADDR1: IC17.16, IC27.16, IC41.16, IC49.16, X1.A4
ADDR2: IC17.14, IC27.14, IC41.14, IC49.14, X1.A5
ADDR3: IC17.12, IC27.12, IC41.12, IC49.12, X1.A6
ADDR4: IC17.9, IC27.9, IC41.9, IC49.9, X1.A7
ADDR5: IC17.7, IC27.7, IC41.7, IC49.7, X1.A8
ADDR6: IC17.5, IC27.5, IC41.5, IC49.5, X1.A9
ADDR7: IC17.3, IC27.3, IC41.3, IC49.3, X1.A10
ADDR8: IC18.18, IC28.18, IC42.18, IC50.18, X1.A11
ADDR9: IC18.16, IC28.16, IC42.16, IC50.16, X1.A12
ADDR10: IC18.14, IC28.14, IC42.14, IC50.14, X1.A13
ADDR11: IC18.12, IC28.12, IC42.12, IC50.12, X1.A14
ADDR12: IC18.9, IC28.9, IC42.9, IC50.9, X1.A15
ADDR13: IC18.7, IC28.7, IC42.7, IC50.7, X1.A16
ADDR14: IC18.5, IC28.5, IC42.5, IC50.5, X1.A17
ADDR15: IC18.3, IC28.3, IC42.3, IC50.3, X1.A18
ADDR-REG-ID0: IC38.2, X1.C3
ADDR-REG-ID1: IC38.3, X1.C4
ADDR-REG-ID2: IC38.14, X1.C5
ADDR-REG-ID3: IC38.13, X1.C6
BUS-DIR: IC34.4, IC35.1, IC36.1, IC37.1
DATA0: IC35.2, IC37.2, X1.A19
DATA1: IC35.3, IC37.3, X1.A20
DATA2: IC35.4, IC37.4, X1.A21
DATA3: IC35.5, IC37.5, X1.A22
DATA4: IC35.6, IC37.6, X1.A23
DATA5: IC35.7, IC37.7, X1.A24
DATA6: IC35.8, IC37.8, X1.A25
DATA7: IC35.9, IC37.9, X1.A26
DATA8: IC36.2, X1.A27
DATA9: IC36.3, X1.A28
DATA10: IC36.4, X1.A29
DATA11: IC36.5, X1.A30
DATA12: IC36.6, X1.B3
DATA13: IC36.7, X1.B4
DATA14: IC36.8, X1.B5
DATA15: IC36.9, X1.B6
GND: C1.2, C2.2, C3.2, C4.2, C5.2, C6.2, C7.2, C8.2, C9.2, C10.2, C11.2, C12.2, C13.2, C14.2, C15.2, C16.2, C17.2, C18.2, C19.2, C20.2, C21.2, C22.2, C23.2, C24.2, C25.2, C26.2, C27.2, C28.2, C29.2, C30.2, C31.2, C32.2, C33.2, C34.2, C35.2, C36.2, C37.2, C38.2, C39.2, C40.2, C41.2, C42.2, C43.2, C44.2, C45.2, C46.2, C47.2, IC1.7, IC2.7, IC3.8, IC4.8, IC5.8, IC6.8, IC7.10, IC8.10, IC9.8, IC10.8, IC11.8, IC12.8, IC13.10, IC14.10, IC15.7, IC17.10, IC18.10, IC19.8, IC20.8, IC21.8, IC22.8, IC23.10, IC24.10, IC25.7, IC26.7, IC27.10, IC28.10, IC29.8, IC30.8, IC31.7, IC32.8, IC33.8, IC34.1, IC34.5, IC34.7, IC34.8, IC35.10, IC36.10, IC37.10, IC38.8, IC40.4, IC40.5, IC40.7, IC40.9, IC40.10, IC40.12, IC40.13, IC41.10, IC42.10, IC43.8, IC44.8, IC45.10, IC46.10, IC47.7, IC49.10, IC50.10, PWR0.K, X1.A1, X1.A32, X1.B1, X1.B32, X1.C1, X1.C32
unnamed: IC31.8, IC35.19, IC36.19
unnamed: IC9.13, IC10.4
unnamed: IC9.12, IC10.5
unnamed: IC10.13, IC11.4
unnamed: IC10.12, IC11.5
unnamed: IC11.13, IC12.4
unnamed: IC11.12, IC12.5
unnamed: IC9.11, IC10.11, IC15.8
unnamed: IC9.5, IC15.3
unnamed: IC3.13, IC4.4
unnamed: IC3.12, IC4.5
unnamed: IC4.13, IC5.4
unnamed: IC4.12, IC5.5
unnamed: IC5.13, IC6.4
unnamed: IC5.12, IC6.5
unnamed: IC1.8, IC3.11, IC4.11
unnamed: IC1.3, IC3.5
unnamed: IC1.6, IC3.4
unnamed: IC31.3, IC32.1
unnamed: IC2.3, IC7.1, IC7.19
unnamed: IC2.6, IC8.1, IC8.19
unnamed: IC1.11, IC5.11, IC6.11
unnamed: IC9.4, IC15.6
unnamed: IC31.6, IC32.15
unnamed: IC2.8, IC13.1, IC13.19
unnamed: IC2.11, IC14.1, IC14.19
unnamed: IC11.11, IC12.11, IC15.11
unnamed: IC9.3, IC13.11, IC17.2
unnamed: IC9.2, IC13.13, IC17.4
unnamed: IC9.6, IC13.15, IC17.6
unnamed: IC9.7, IC13.17, IC17.8
unnamed: IC10.3, IC13.2, IC17.11
unnamed: IC10.2, IC13.4, IC17.13
unnamed: IC10.6, IC13.6, IC17.15
unnamed: IC10.7, IC13.8, IC17.17
unnamed: IC11.3, IC14.11, IC18.2
unnamed: IC31.11, IC37.19
unnamed: IC11.2, IC14.13, IC18.4
unnamed: IC11.6, IC14.15, IC18.6
unnamed: IC11.7, IC14.17, IC18.8
unnamed: IC31.9, IC34.10
unnamed: IC31.10, IC31.12, IC34.11
unnamed: IC32.5, J1.3
unnamed: PWR0.A, R1.1
unnamed: IC38.15, IC40.3
unnamed: IC32.6, J1.5
unnamed: IC32.7, J1.7
unnamed: IC32.11, J2.3
unnamed: IC32.10, J2.5
unnamed: IC32.9, J2.7
unnamed: IC38.11, J3.3
unnamed: IC38.10, J3.5
unnamed: IC38.9, J3.7
unnamed: IC12.3, IC14.2, IC18.11
unnamed: IC12.2, IC14.4, IC18.13
unnamed: IC12.6, IC14.6, IC18.15
unnamed: IC12.7, IC14.8, IC18.17
unnamed: IC19.13, IC20.4
unnamed: IC19.12, IC20.5
unnamed: IC20.13, IC21.4
unnamed: IC20.12, IC21.5
unnamed: IC21.13, IC22.4
unnamed: IC21.12, IC22.5
unnamed: IC19.11, IC20.11, IC25.8
unnamed: IC19.5, IC25.3
unnamed: IC19.4, IC25.6
unnamed: IC23.1, IC23.19, IC26.3
unnamed: IC24.1, IC24.19, IC26.6
unnamed: IC21.11, IC22.11, IC25.11
unnamed: IC19.3, IC23.11, IC27.2
unnamed: IC19.2, IC23.13, IC27.4
unnamed: IC19.6, IC23.15, IC27.6
unnamed: IC19.7, IC23.17, IC27.8
unnamed: IC20.3, IC23.2, IC27.11
unnamed: IC20.2, IC23.4, IC27.13
unnamed: IC20.6, IC23.6, IC27.15
unnamed: IC20.7, IC23.8, IC27.17
unnamed: IC21.3, IC24.11, IC28.2
unnamed: IC21.2, IC24.13, IC28.4
unnamed: IC21.6, IC24.15, IC28.6
unnamed: IC21.7, IC24.17, IC28.8
unnamed: IC22.3, IC24.2, IC28.11
unnamed: IC22.2, IC24.4, IC28.13
unnamed: IC22.6, IC24.6, IC28.15
unnamed: IC22.7, IC24.8, IC28.17
unnamed: IC29.13, IC30.4
unnamed: IC29.12, IC30.5
unnamed: IC30.13, IC43.4
unnamed: IC30.12, IC43.5
unnamed: IC43.13, IC44.4
unnamed: IC43.12, IC44.5
unnamed: IC29.11, IC30.11, IC47.8
unnamed: IC29.5, IC47.3
unnamed: IC29.4, IC47.6
unnamed: IC26.8, IC45.1, IC45.19
unnamed: IC26.11, IC46.1, IC46.19
unnamed: IC43.11, IC44.11, IC47.11
unnamed: IC29.3, IC45.11, IC49.2
unnamed: IC29.2, IC45.13, IC49.4
unnamed: IC29.6, IC45.15, IC49.6
unnamed: IC29.7, IC45.17, IC49.8
unnamed: IC30.3, IC45.2, IC49.11
unnamed: IC30.2, IC45.4, IC49.13
unnamed: IC30.6, IC45.6, IC49.15
unnamed: IC30.7, IC45.8, IC49.17
unnamed: IC43.3, IC46.11, IC50.2
unnamed: IC43.2, IC46.13, IC50.4
unnamed: IC43.6, IC46.15, IC50.6
unnamed: IC43.7, IC46.17, IC50.8
unnamed: IC44.3, IC46.2, IC50.11
unnamed: IC44.2, IC46.4, IC50.13
unnamed: IC44.6, IC46.6, IC50.15
unnamed: IC44.7, IC46.8, IC50.17
unnamed: IC3.3, IC7.11, IC41.2
unnamed: IC3.2, IC7.13, IC41.4
unnamed: IC3.6, IC7.15, IC41.6
unnamed: IC3.7, IC7.17, IC41.8
unnamed: IC4.3, IC7.2, IC41.11
unnamed: IC4.2, IC7.4, IC41.13
unnamed: IC4.6, IC7.6, IC41.15
unnamed: IC4.7, IC7.8, IC41.17
unnamed: IC5.3, IC8.11, IC42.2
unnamed: IC5.2, IC8.13, IC42.4
unnamed: IC5.6, IC8.15, IC42.6
unnamed: IC5.7, IC8.17, IC42.8
unnamed: IC6.3, IC8.2, IC42.11
unnamed: IC6.2, IC8.4, IC42.13
unnamed: IC6.6, IC8.6, IC42.15
unnamed: IC6.7, IC8.8, IC42.17
REG-LD-ID0: IC33.14, X1.B13
REG-LD-ID1: IC33.13, X1.B14
REG-LD-ID2: IC32.14, X1.B15
REG-LD-ID3: IC32.13, X1.B16
REG-RD-ID0: IC33.2, X1.B9
REG-RD-ID1: IC33.3, X1.B10
REG-RD-ID2: IC32.2, X1.B11
REG-RD-ID3: IC32.3, X1.B12
RESET: IC3.14, IC4.14, IC5.14, IC6.14, IC9.14, IC10.14, IC11.14, IC12.14, IC19.14, IC20.14, IC21.14, IC22.14, IC29.14, IC30.14, IC34.3, IC43.14, IC44.14
VCC: C1.1, C2.1, C3.1, C4.1, C5.1, C6.1, C7.1, C8.1, C9.1, C10.1, C11.1, C12.1, C13.1, C14.1, C15.1, C16.1, C17.1, C18.1, C19.1, C20.1, C21.1, C22.1, C23.1, C24.1, C25.1, C26.1, C27.1, C28.1, C29.1, C30.1, C31.1, C32.1, C33.1, C34.1, C35.1, C36.1, C37.1, C38.1, C39.1, C40.1, C41.1, C42.1, C43.1, C44.1, C45.1, C46.1, C47.1, IC1.14, IC2.14, IC3.16, IC4.16, IC5.16, IC6.16, IC7.20, IC8.20, IC9.16, IC10.16, IC11.16, IC12.16, IC13.20, IC14.20, IC15.14, IC17.20, IC18.20, IC19.16, IC20.16, IC21.16, IC22.16, IC23.20, IC24.20, IC25.14, IC26.14, IC27.20, IC28.20, IC29.16, IC30.16, IC31.14, IC32.16, IC33.16, IC34.14, IC35.20, IC36.20, IC37.20, IC38.16, IC40.14, IC41.20, IC42.20, IC43.16, IC44.16, IC45.20, IC46.20, IC47.14, IC49.20, IC50.20, R1.2, RN1.1, RN2.1, X1.A2, X1.A31, X1.B2, X1.B31, X1.C2, X1.C31
